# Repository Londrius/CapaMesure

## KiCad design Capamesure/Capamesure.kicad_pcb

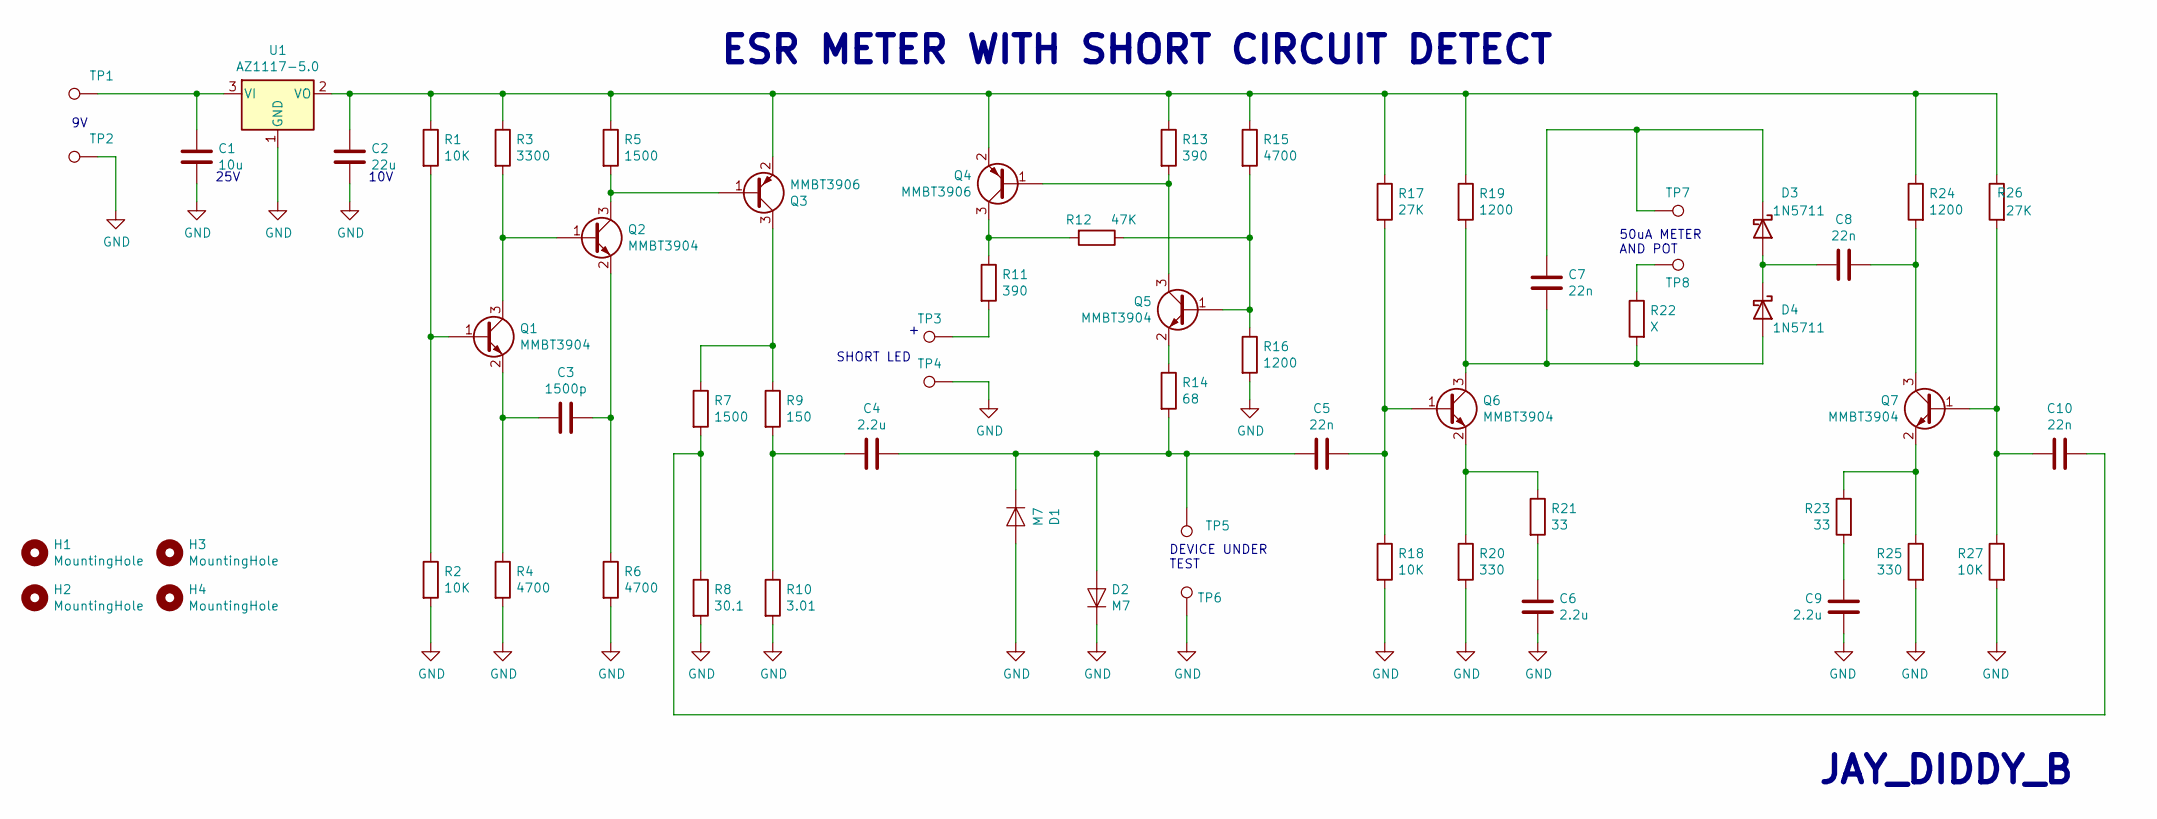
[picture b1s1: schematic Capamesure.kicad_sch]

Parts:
C1: 10u; C_0805_2012Metric; LCSC C15850
C2: 22u; C_0805_2012Metric; LCSC C45783
C3: 1500p; C_0805_2012Metric; LCSC C1717
C4, C6, C9: 2.2u; C_1206_3216Metric; LCSC C50254
C5, C7, C8, C10: 22n; C_0805_2012Metric; LCSC C1729
D1, D2: M7; D_SMA_Handsoldering; LCSC C95872
D3, D4: 1N5711; D_SOD-123; LCSC C154843
H1, H2, H3, H4: MountingHole; MountingHole_3.7mm_Pad
Q1, Q2, Q5, Q6, Q7: MMBT3904; SOT-23; LCSC C20526
Q3, Q4: MMBT3906; SOT-23; LCSC C181120
R1, R2, R18, R27: 10K; R_0805_2012Metric; LCSC C17414
R3: 3300; R_0805_2012Metric; LCSC C26010
R4, R6, R15: 4700; R_0805_2012Metric; LCSC C17673
R5, R7: 1500; R_0805_2012Metric; LCSC C4310
R8: 30.1; R_0805_2012Metric; LCSC C218507
R9: 150; R_0805_2012Metric; LCSC C17471
R10: 3.01; R_0805_2012Metric; LCSC C137532
R11, R13: 390; R_0805_2012Metric; LCSC C17655
R12: 47K; R_0805_2012Metric; LCSC C17713
R14: 68; R_0805_2012Metric; LCSC C17802
R16, R19, R24: 1200; R_0805_2012Metric; LCSC C17379
R17, R26: 27K; R_0805_2012Metric; LCSC C17593
R20, R25: 330; R_0805_2012Metric; LCSC C17630
R21, R23: 33; R_0805_2012Metric; LCSC C204426
R22: X; R_0805_2012Metric
TP1, TP2, TP3, TP4, TP5, TP6, TP7, TP8: TestPoint; keystone_1514_93_hole
U1: AZ1117-5.0; SOT-223-3_TabPin2; LCSC C6187

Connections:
GND: C1.2, C2.2, C6.1, C9.1, D1.2, D2.1, R2.2, R4.2, R6.2, R8.2, R10.2, R16.2, R18.2, R20.2, R25.2, R27.2, TP2.1, TP4.1, TP6.1, U1.1 (GND)
unnamed: C4.1, C5.2, D1.1, D2.2, R14.2, TP5.1
unnamed: C4.2, R9.2, R10.1
unnamed: C6.2, R21.2
unnamed: C9.2, R23.2
unnamed: C10.2, R7.2, R8.1
unnamed: C8.2, D3.2 (A), D4.1 (K)
unnamed: C7.2, D3.1 (K), TP7.1
unnamed: C7.1, D4.2 (A), Q6.3 (C), R19.2, R22.2
unnamed: Q1.1 (B), R1.2, R2.1
unnamed: Q1.3 (C), Q2.1 (B), R3.2
unnamed: C3.2, Q1.2 (E), R4.1
unnamed: Q2.3 (C), Q3.1 (B), R5.2
unnamed: C3.1, Q2.2 (E), R6.1
unnamed: Q3.3 (C), R7.1, R9.1
unnamed: C2.1, Q3.2 (E), Q4.2 (E), R1.1, R3.1, R5.1, R13.1, R15.1, R17.1, R19.1, R24.1, R26.1, U1.2 (VO)
unnamed: Q4.1 (B), Q5.3 (C), R13.2
unnamed: Q4.3 (C), R11.1, R12.2
unnamed: Q5.1 (B), R12.1, R15.2, R16.1
unnamed: Q5.2 (E), R14.1
unnamed: C5.1, Q6.1 (B), R17.2, R18.1
unnamed: Q6.2 (E), R20.1, R21.1
unnamed: C10.1, Q7.1 (B), R26.2, R27.1
unnamed: C8.1, Q7.3 (C), R24.2
unnamed: Q7.2 (E), R23.1, R25.1
unnamed: R11.2, TP3.1
unnamed: R22.1, TP8.1
unnamed: C1.1, TP1.1, U1.3 (VI)

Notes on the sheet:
25V
10V
DEVICE UNDER TEST
JAY_DIDDY_B
SHORT LED
50uA METER AND POT
ESR METER WITH SHORT CIRCUIT DETECT

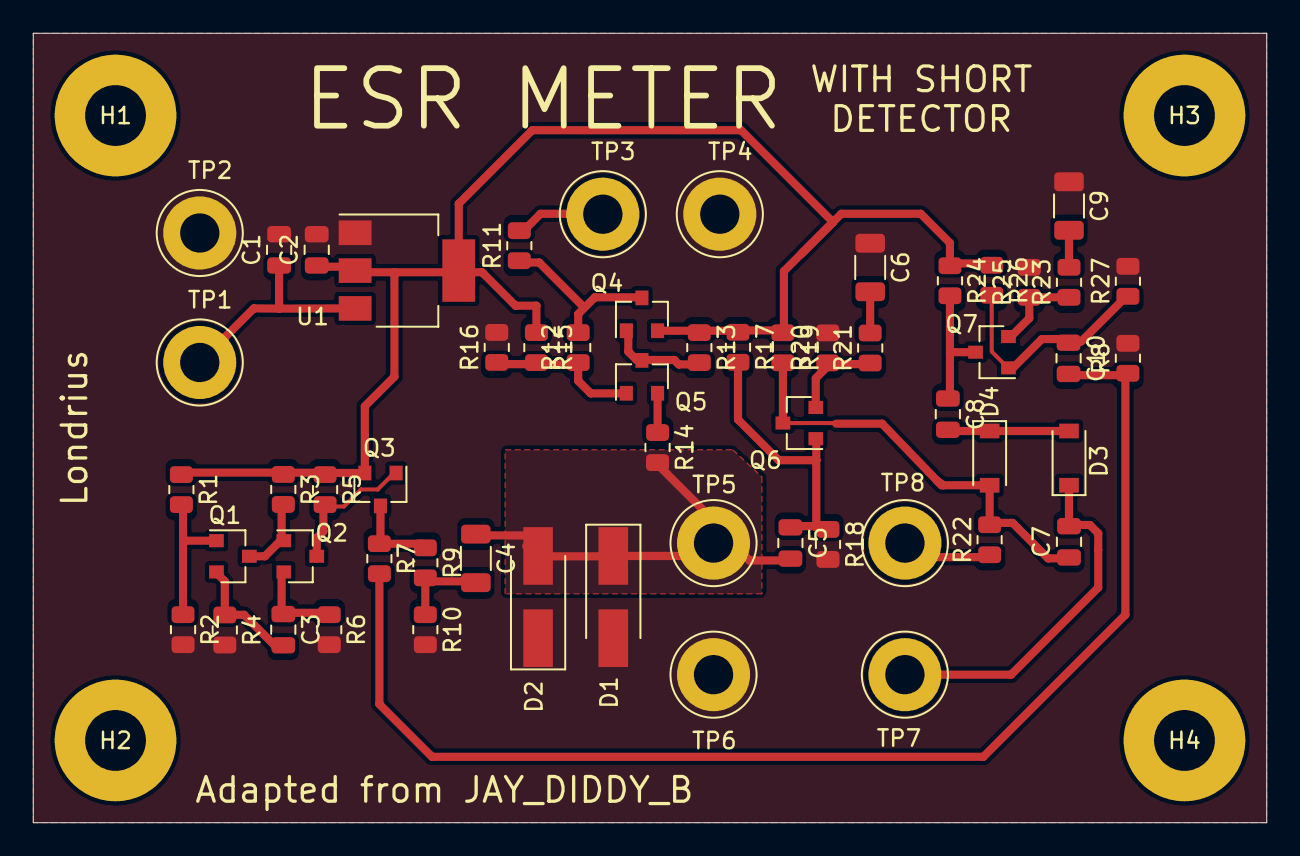
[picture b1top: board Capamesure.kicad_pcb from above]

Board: 2 copper layers, 75.0 x 48.0 mm, 61 parts (0 on the bottom side), 28 nets.

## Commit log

2024-07-24 Clone from EEV Blog
    saved data from eev blog
2024-07-25 Capacitor & Resistoir changes
    changed footprint
2024-07-25 lib added
    added lib
2024-07-29 footprints
    foot
